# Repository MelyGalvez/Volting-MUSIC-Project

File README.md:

# Volting Music Project
Extension of Volting Music project to a more immersive environnement in Tongji University.

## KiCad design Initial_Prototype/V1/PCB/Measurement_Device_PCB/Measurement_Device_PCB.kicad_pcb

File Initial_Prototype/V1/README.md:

# Initial Prototyp - V1

This first version of the prototyp allow the user to create sounds with movements of his own body (hands and chest).

## Prerequisites

### Hardware

- 1 Arduino UNO and it's connection cable.
- 1 IMU GY-85.
- 2 Ultrasound sensors RCW-0001 (as long as you have the ‘TRIG’ and ‘ECHO’ pins, you can use any 4-pin component of your choice).
- 2 4-Pin push-button switches.
- 3 TH LEDs respectively red, yellow and green.
- 5 Security TH resistors of 220 Ohm.
- 2 1-Metre cable leads, male to 4-pin female.
- 2 1-Metre cable leads, male to 3-pin female.
- 1 Breadboard, measuring at least 10 × 10 cm (if you can print your own PCB it's better, the code is in the [Measurement_Device_PCB](https://github.com/MelyGalvez/Volting-MUSIC-Project/tree/main/Initial_Prototype/V1/PCB/Measurement_Device_PCB) file).
- 1 Soldering iron and some tin.

### Software

- Arduino IDE
- Processing-3.5.4

## PCB

Assemble / Solder your board by following the [routing](https://github.com/MelyGalvez/Volting-MUSIC-Project/tree/main/Initial_Prototype/V1/PCB).

## Run code

- Open the [Volting_MUSIC_Arduino_Prototype_V1](https://github.com/MelyGalvez/Volting-MUSIC-Project/tree/main/Initial_Prototype/V1/Codes/Volting_MUSIC_Arduino_Prototype_V1) file.
- Connect your PCB to your machine, select the right COM and board (UNO).
- Download the Arduino code via the IDE.
- You can check the serial monitor to see data sent at the right rate. Do not forget to close this monitor before the next steps. If you don't it will block the COM port.
- Open the [Volting_MUSIC_Processing_Prototype_V1](https://github.com/MelyGalvez/Volting-MUSIC-Project/tree/main/Initial_Prototype/V1/Codes/Volting_MUSIC_Processing_Prototype_V1) file.
- Run the code and enjoy.

## Conclusion

This first version of the prototype works, but is not particularly effective, as the GY-85 IMU is an imprecise sensor. It is therefore difficult to choose the right location for mapping.

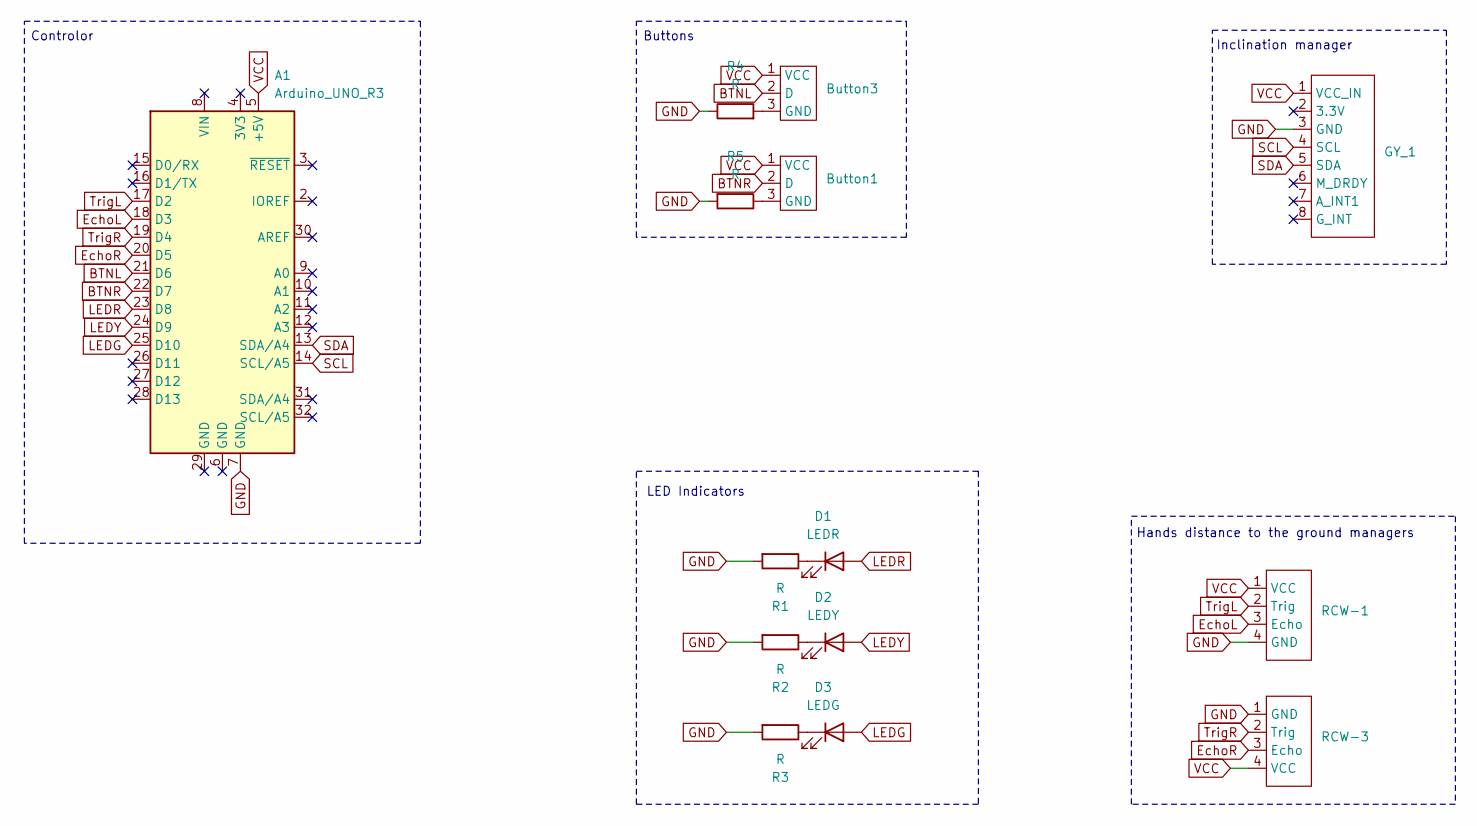
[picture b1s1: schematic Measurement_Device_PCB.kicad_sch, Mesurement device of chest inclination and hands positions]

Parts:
A1: Arduino_UNO_R3
Button1, Button3: Button
D1: LEDR; LED
D2: LEDY; LED
D3: LEDG; LED
GY_1: GY_85
R1, R2, R3, R4, R5: R
RCW-1, RCW-3: RCW-0001

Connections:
BTNL: A1.21 (D6), Button3.2 (D)
BTNR: A1.22 (D7), Button1.2 (D)
EchoL: A1.18 (D3), RCW-1.3 (Echo)
EchoR: A1.20 (D5), RCW-3.3 (Echo)
GND: A1.7 (GND), GY_1.3 (GND), R1.2, R2.2, R3.2, R4.1, R5.2, RCW-1.4 (GND), RCW-3.1 (GND)
LEDG: A1.25 (D10), D3.2 (A)
LEDR: A1.23 (D8), D1.2 (A)
LEDY: A1.24 (D9), D2.2 (A)
unnamed: Button1.3 (GND), R5.1
unnamed: Button3.3 (GND), R4.2
unnamed: D1.1 (K), R1.1
unnamed: D2.1 (K), R2.1
unnamed: D3.1 (K), R3.1
SCL: A1.14 (SCL/A5), GY_1.4 (SCL)
SDA: A1.13 (SDA/A4), GY_1.5 (SDA)
TrigL: A1.17 (D2), RCW-1.2 (Trig)
TrigR: A1.19 (D4), RCW-3.2 (Trig)
VCC: A1.5 (+5V), Button1.1 (VCC), Button3.1 (VCC), GY_1.1 (VCC_IN), RCW-1.1 (VCC), RCW-3.4 (VCC)

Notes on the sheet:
Controlor
Buttons
LED Indicators
Hands distance to the ground managers
Inclination manager

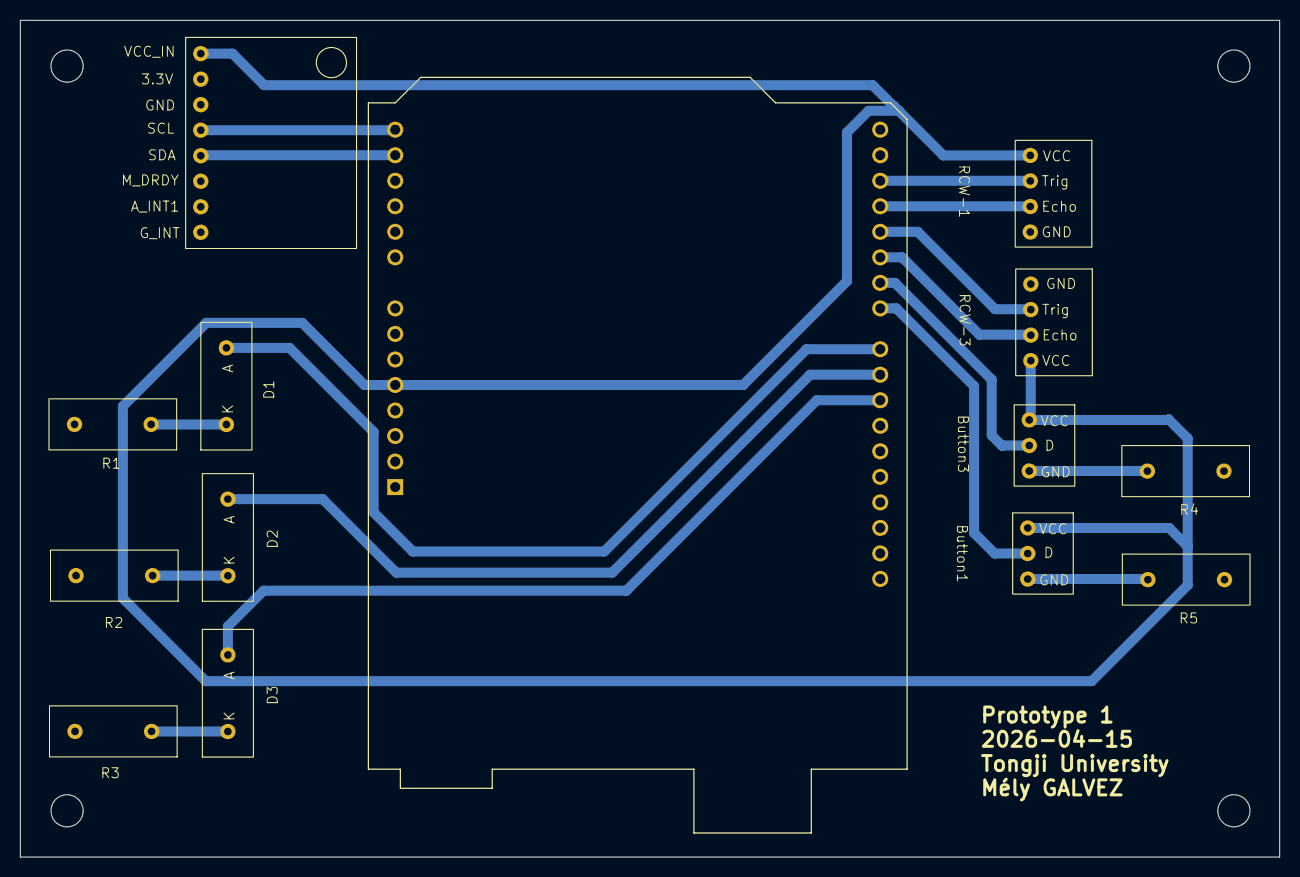
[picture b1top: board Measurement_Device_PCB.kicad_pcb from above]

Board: 2 copper layers, 125.3 x 83.2 mm, 14 parts (0 on the bottom side), 18 nets.

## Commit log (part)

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2026-04-13 Measurements code
2026-04-13 Prototype's code uploading
2026-04-13 Rename stl file
2026-04-15 New PCB
2026-04-15 PCB Update
2026-04-21 Measurements codes
2026-04-21 New meassurement code importation
2026-04-23 Updates of P1 Arduino code
2026-04-23 Updates and modifications
2026-04-23 Readme update
2026-04-23 Measurement codes updates
2026-05-21 Suit Dev
2026-05-25 IMU PCB Design
2026-05-26 IMU Gerber files
2026-05-27 Update IMU PCB and Upload Central Unit PCB
2026-05-29 PCB Design
2026-06-30 Beginning of software
